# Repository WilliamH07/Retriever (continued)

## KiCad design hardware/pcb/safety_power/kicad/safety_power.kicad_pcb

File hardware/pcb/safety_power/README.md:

# safety_power

> ⚠️ **v2.0-draft — do not manufacture before M1, M2, M10, M12, PACK_ID, P1–P3 and a
> review by an electronics engineer.** Schematic and layout are generated and checked
> (ERC/DRC below); nothing has been built, measured or reviewed. This board switches
> 42 V / 30 A on a 474 Wh lithium pack. Every choice, every computed value, what is not
> verified and what an expert must look at: [`decisions.md`](decisions.md) (French).
> Brief: [`cahier-des-charges.md`](cahier-des-charges.md).

| | |
|---|---|
| Status | **v2.0-draft** — ERC 0 · DRC 0 (`--schematic-parity --severity-all`) · 0 unconnected · parity 0. Not fabricated, not reviewed |
| Size | 210 × 160 mm, 4 layers, 2 oz outer copper, 6 × M3 (unplated, no chassis bond) |
| Parts | 344 symbols, 350 footprints; JLCPCB BOM 111 lines / 298 placements (THT connectors and modules included); hand-fitted: 4 fuse holders, ESP32 sockets, ring lugs |
| Contactor | `TPS48100QDGXRQ1` (in stock at JLCPCB, C43131316) + 2 × `IPB017N10N5LF` back-to-back, 1 mΩ 4-wire shunt, SCP ≈ 99 A / 100 µs latched |
| Rails (upstream of the contactor) | 5 V 3.5 A and 12 V AUX 2 A on `TPS54360B`; 12 V 30 W isolated `URB4812YMD-30WR3`; 3.3 V `AP2112K` |
| Sources | [`kicad/`](kicad/) — KiCad 10 project, **generated** by [`scripts/build.py`](scripts/build.py) (+ [`scripts/splib.py`](scripts/splib.py) for the symbols and footprints KiCad lacks) |
| Fabrication | [`fab/`](fab/) — Gerber zip, JLCPCB BOM and placement, schematic PDF, assembly drawing, renders |

Rebuild everything: `./build.sh` (placement, power copper, Freerouting, then a
clean-up pass by [`scripts/patchroute.py`](scripts/patchroute.py); 30–60 minutes) then
`./fab.sh`. Freerouting is not deterministic: a rebuild gives an equivalent board, not an
identical one, and may leave a connection for the clean-up pass or for hand routing. The
committed board took one hand-placed via (net `EFUSE_FLT_N`, near U14) after that pass. Toolchain: [`../outils.md`](../outils.md). Do not edit the
KiCad files by hand: change `scripts/build.py` and rebuild.

## What it does

The board that decides whether the robot may move.

- **Battery in** on two M5 ring-lug studs (`J1`), after the manual battery switch and the
  MRBF fuse.
- **Static contactor**: `TPS48100-Q1` driving two `IPB017N10N5LF` back to back, common
  source, so the switch blocks both discharge and regeneration. Two independent gate
  drives on `INP1`/`INP2` make a per-transistor stuck-switch test possible (`MID` node
  read by an ADS1115). Bidirectional `SMCJ48CA` across the switch, Schottky freewheel on
  the bus, 150 Ω turn-off gate resistors.
- **Precharge** through an off-board 10 Ω / 25 W resistor (`J13`), P-FET driven by the
  ESP32, not by the controller.
- **Brake chopper**: analogue comparator powered **by the bus itself** through a 100 V LDO,
  42.5 V on / 41.8 V off, 22 Ω / 100 W off-board (`J12`). It also serves as the active bus
  discharge when the ESP32 asks for it with the contactor open.
- **Four motor branches**, each with a MINI 58 V 25 A blade fuse in a PCB holder, a 2 mΩ
  4-wire shunt and an `INA228` whose bus input sits after the fuse (blown-fuse detection).
- **Hotel rails taken upstream of the contactor** (decision D2), so the SAFETY ESP32, the
  `/SAFE` pull-up and `5V_BRAKE` survive an open contactor.
- **SAFETY ESP32** (DevKitC V4 on sockets), CAN (`TCAN1042HV`), the **single** `/SAFE`
  pull-up through the mushroom's NC contact and the single pull-down, a `TPL5010`
  watchdog **latched** by a D flip-flop together with an ACS758 window comparator
  (± 35 A), an isolated BMS UART, the remote BNO085, two fans, two WS2812B strips and a
  temperature input.
- **One ground bond**, `★ GND STAR`, between `GND_LOGIC` and `BUS_N`, silkscreened.

## Layout

Strict zoning: the 42 V power zone across the top 64 mm, the signal zone below, split
along a line where the inner and bottom ground planes change from `BUS_N` to `GND_LOGIC`.
The high-current copper (battery, drain planes, bus bar, branches, chopper) is drawn by
the script as polygons on F.Cu with stitched B.Cu/In1 return planes, and is handed to the
autorouter as planes: Freerouting only routes signals. Clearance on 42 V power copper is
0.5 mm.

**Routing quality is draft quality.** The autorouter used the inner ground layer (In1) for
about 450 short signal segments, which cuts the `GND_LOGIC`/`BUS_N` planes into a lace,
and it routed both switching regulators. Both must be redone by hand before anyone orders
this board (see *Relecture experte* in `decisions.md`).

## Blocking measurements

M1 (BMS cut-off), M2 (pack resistance), M10 (bus capacitance), M12 (driver input
capacitor rating), PACK_ID (pack and BMS labels), P1–P3 (ESP32 module footprint, pin
order, PSRAM variant). See [`docs/measurements/`](../../../docs/measurements/).

Pinout: `boards.safety_power` in [`hardware/icd.yaml`](../../icd.yaml). The board departs
from ICD v1.2 in a few places (ring-lug studs, MINI 58 V fuses, new `5V_BRAKE`
connectors J22/J23, BMS on JST GH): the proposed v1.3 changes are listed at the end of
[`decisions.md`](decisions.md).

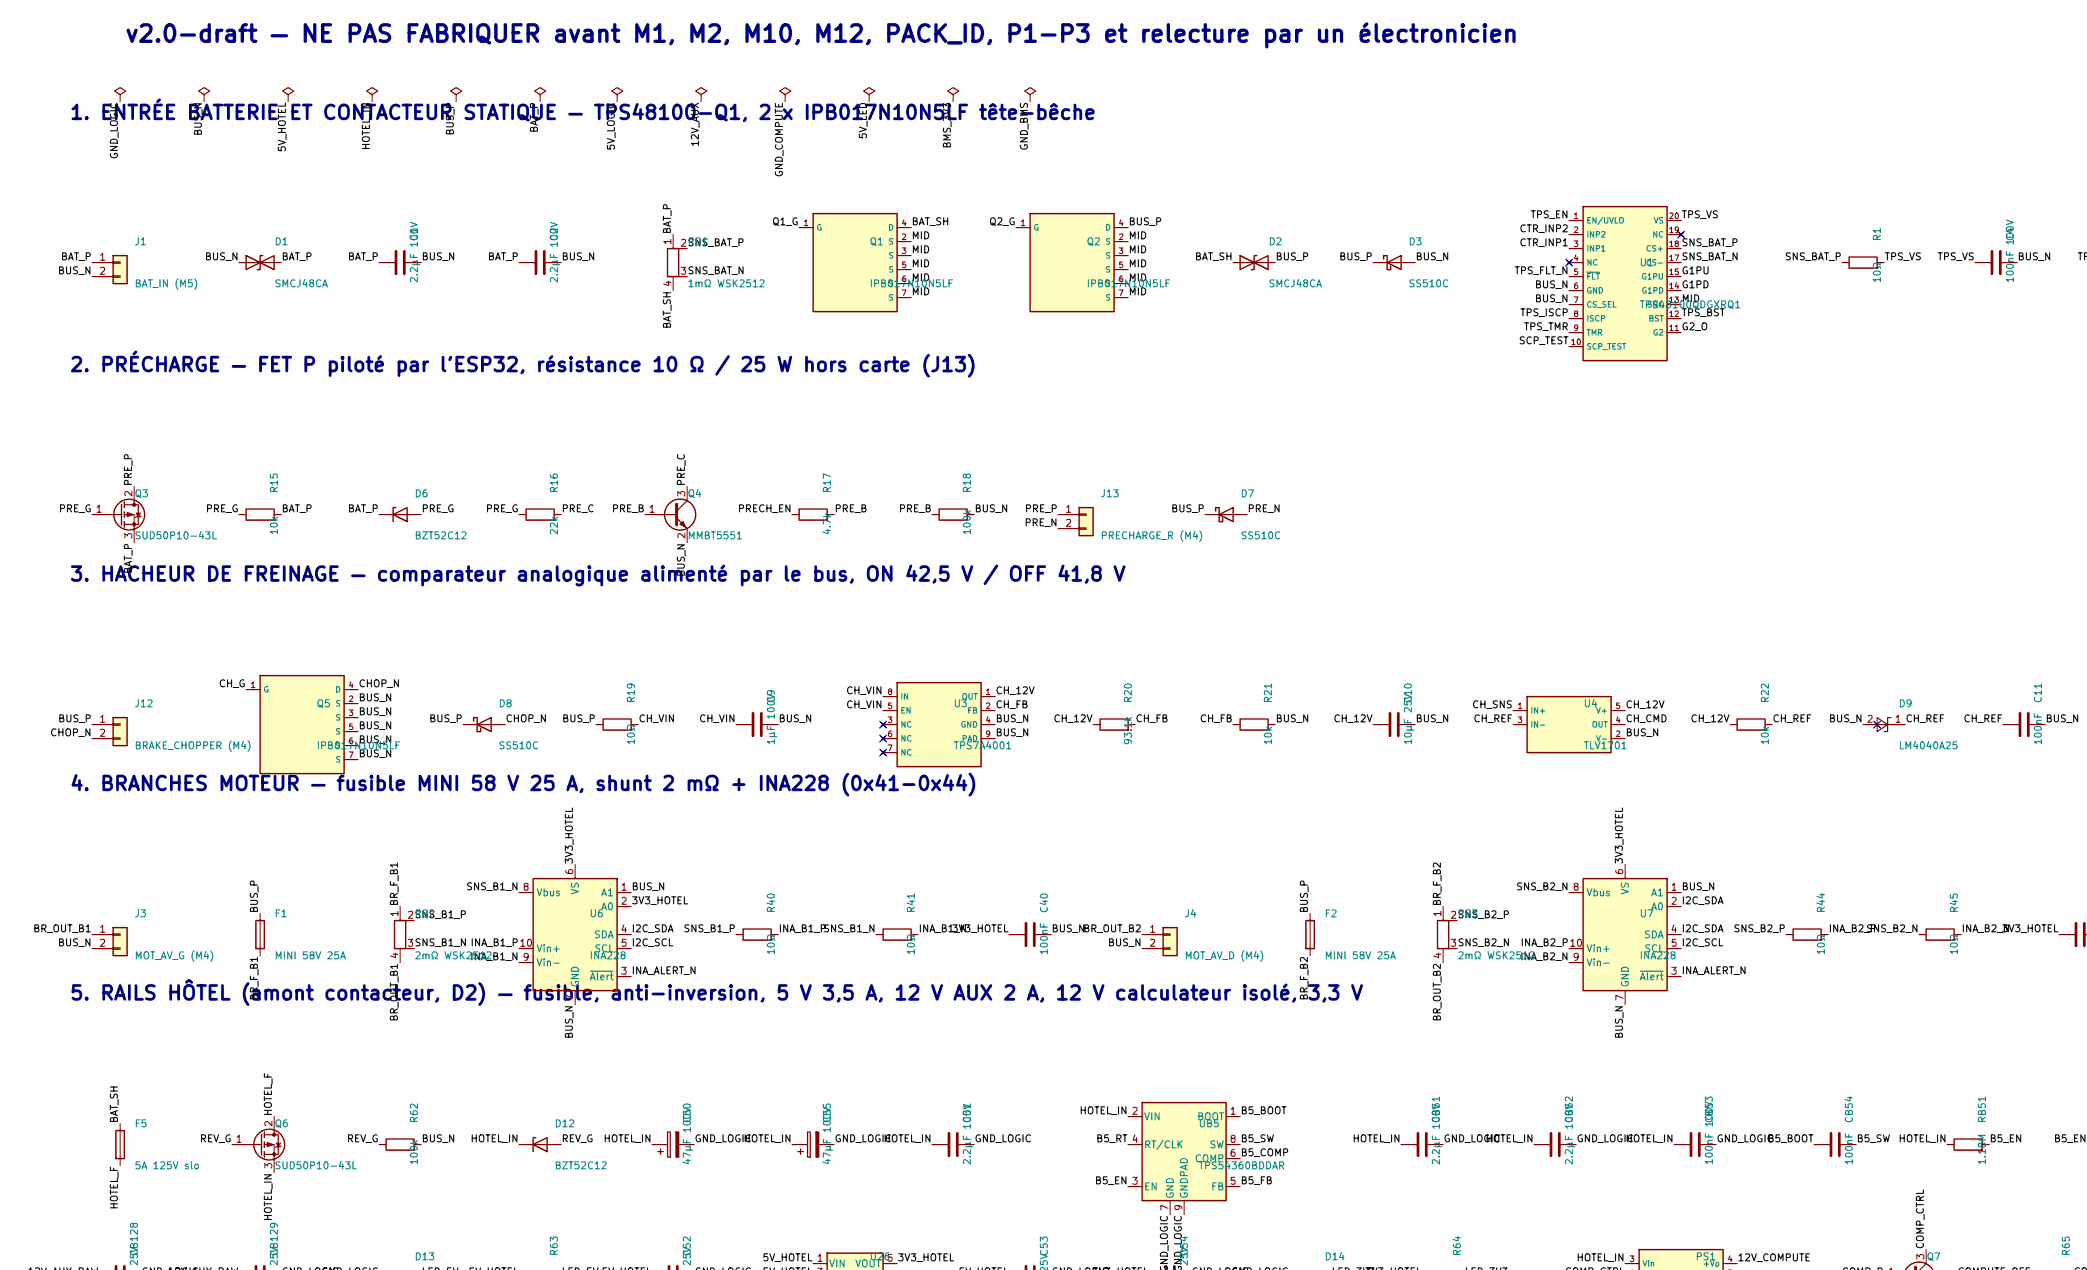
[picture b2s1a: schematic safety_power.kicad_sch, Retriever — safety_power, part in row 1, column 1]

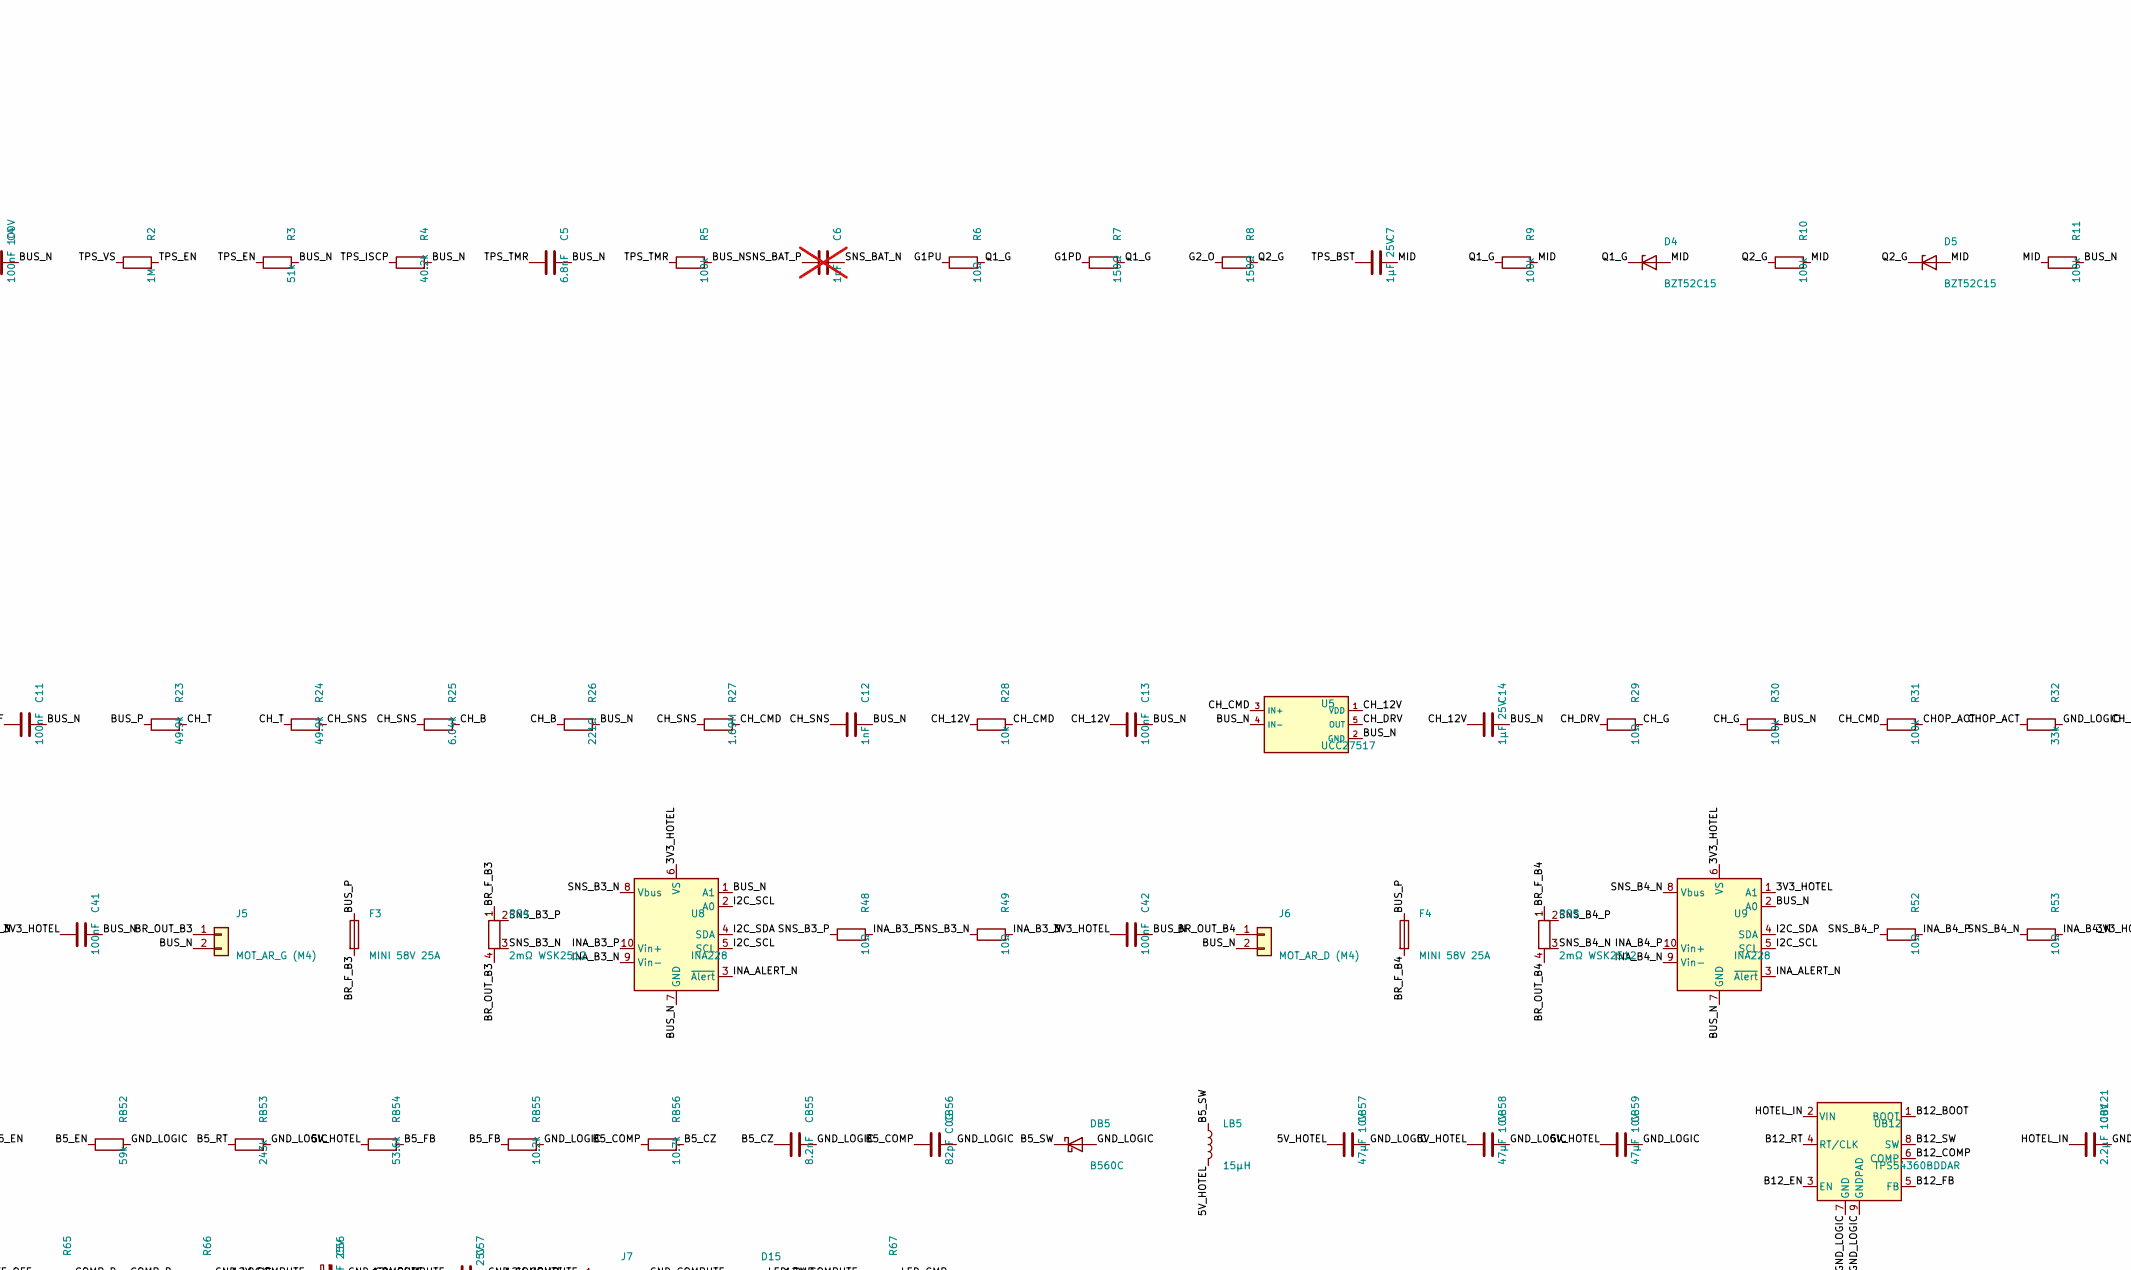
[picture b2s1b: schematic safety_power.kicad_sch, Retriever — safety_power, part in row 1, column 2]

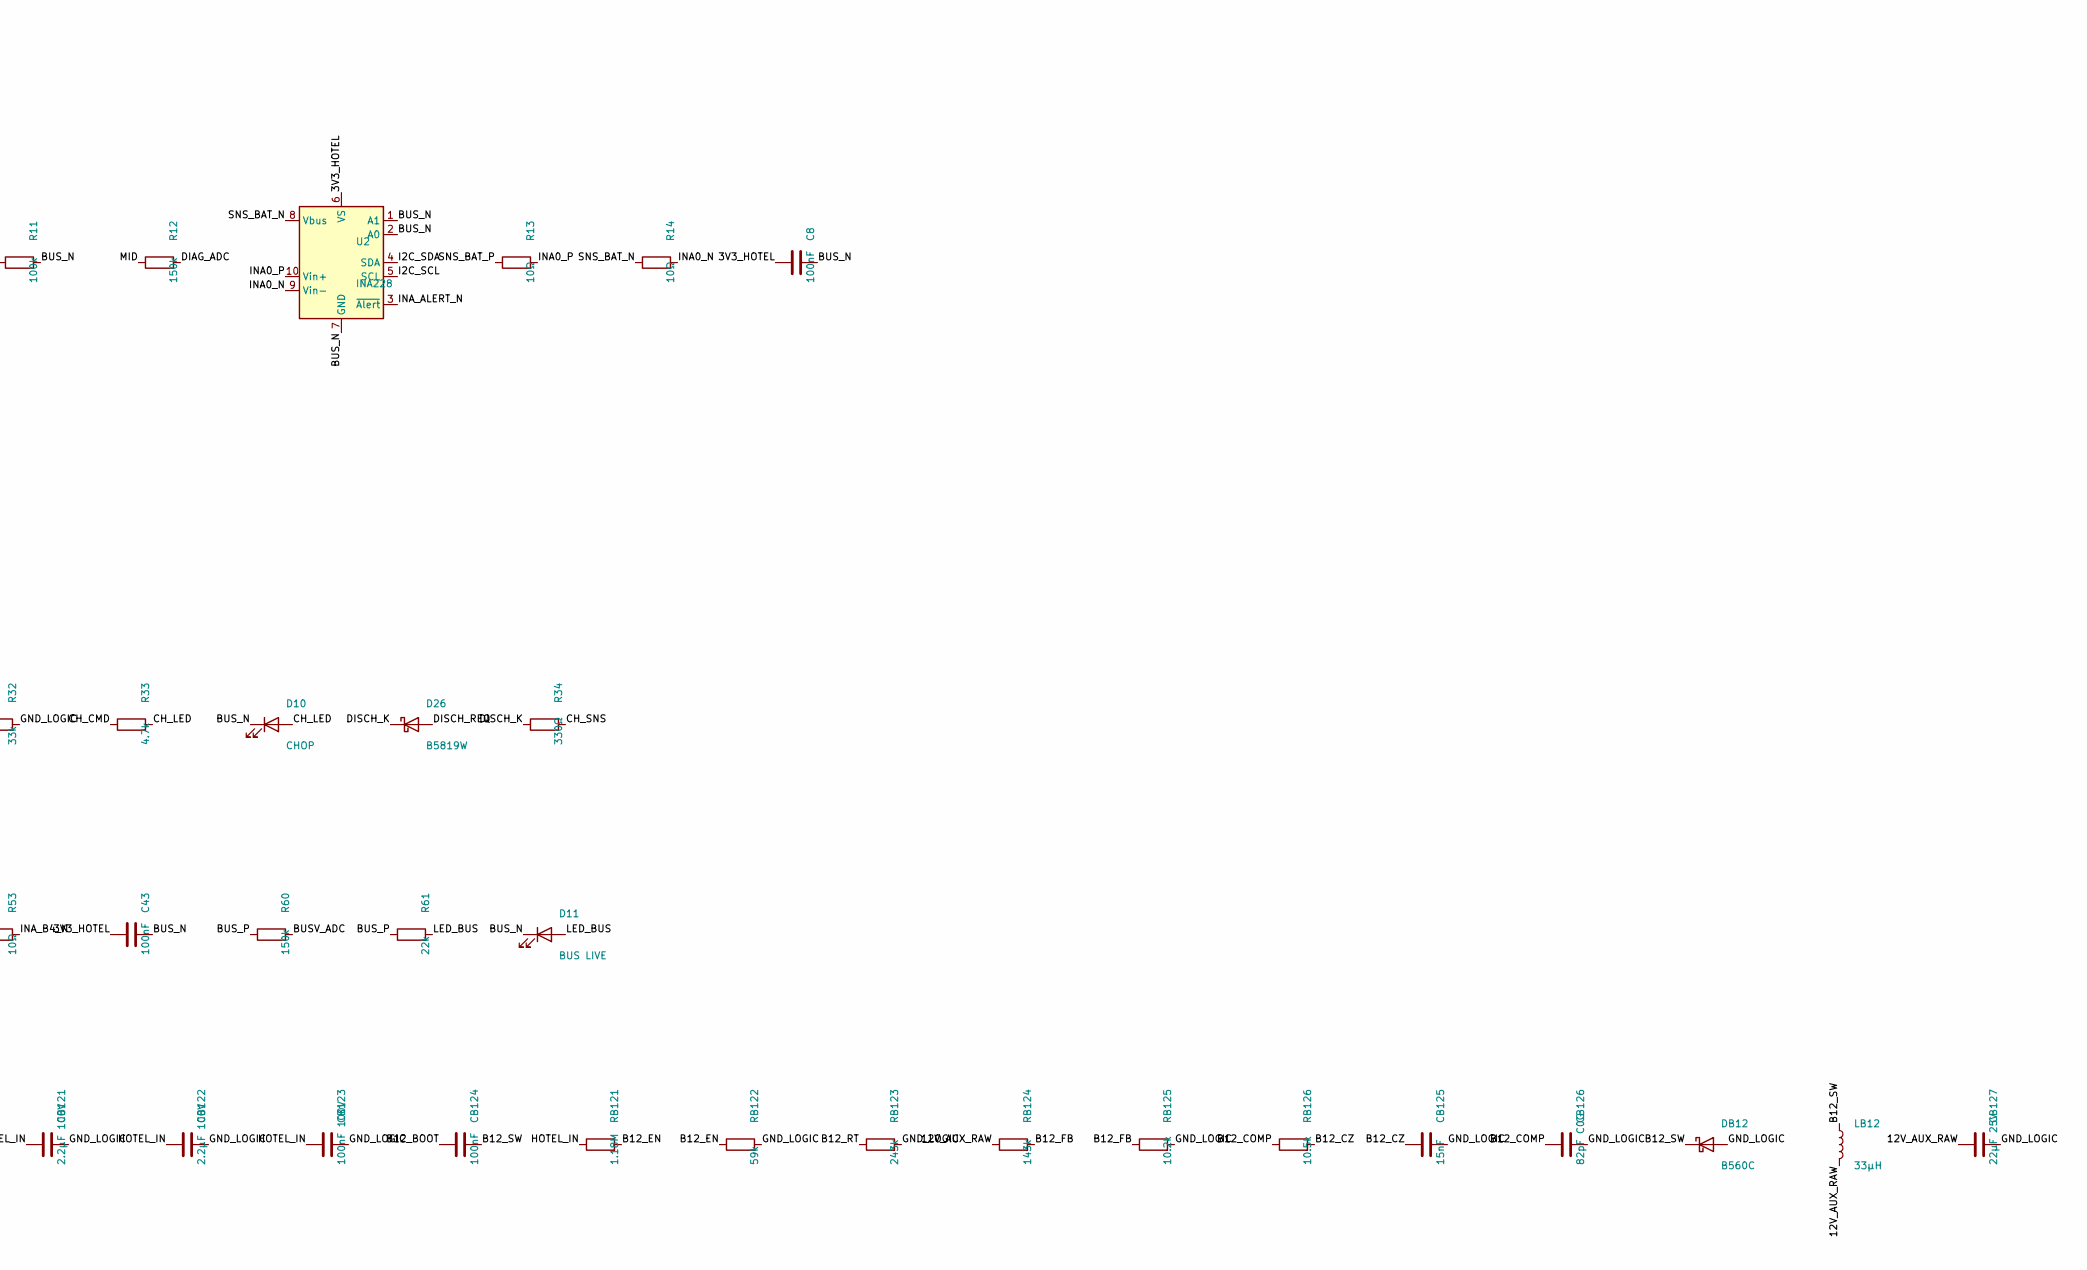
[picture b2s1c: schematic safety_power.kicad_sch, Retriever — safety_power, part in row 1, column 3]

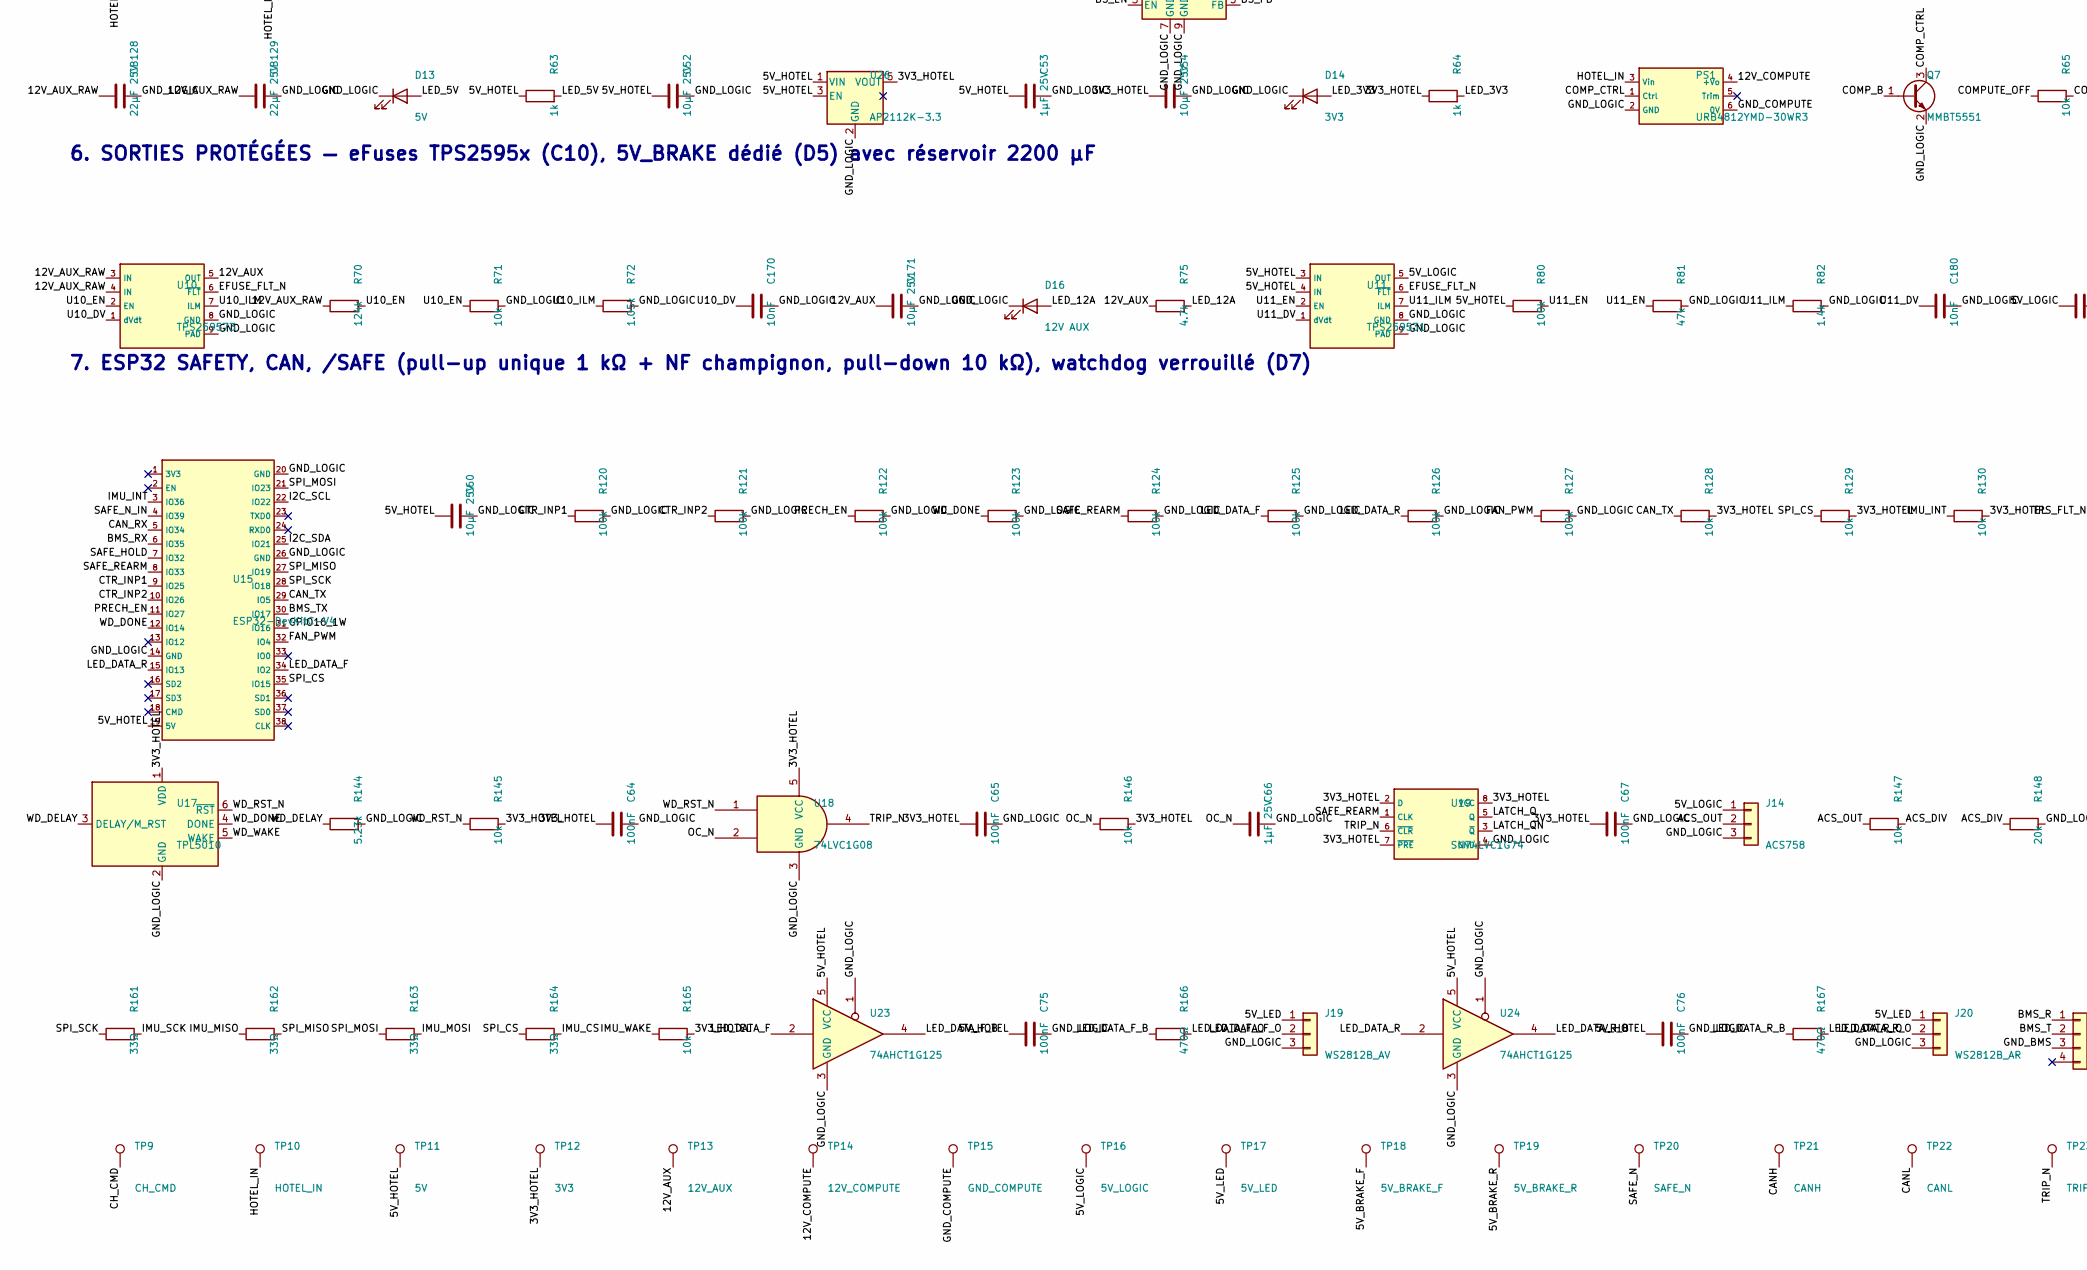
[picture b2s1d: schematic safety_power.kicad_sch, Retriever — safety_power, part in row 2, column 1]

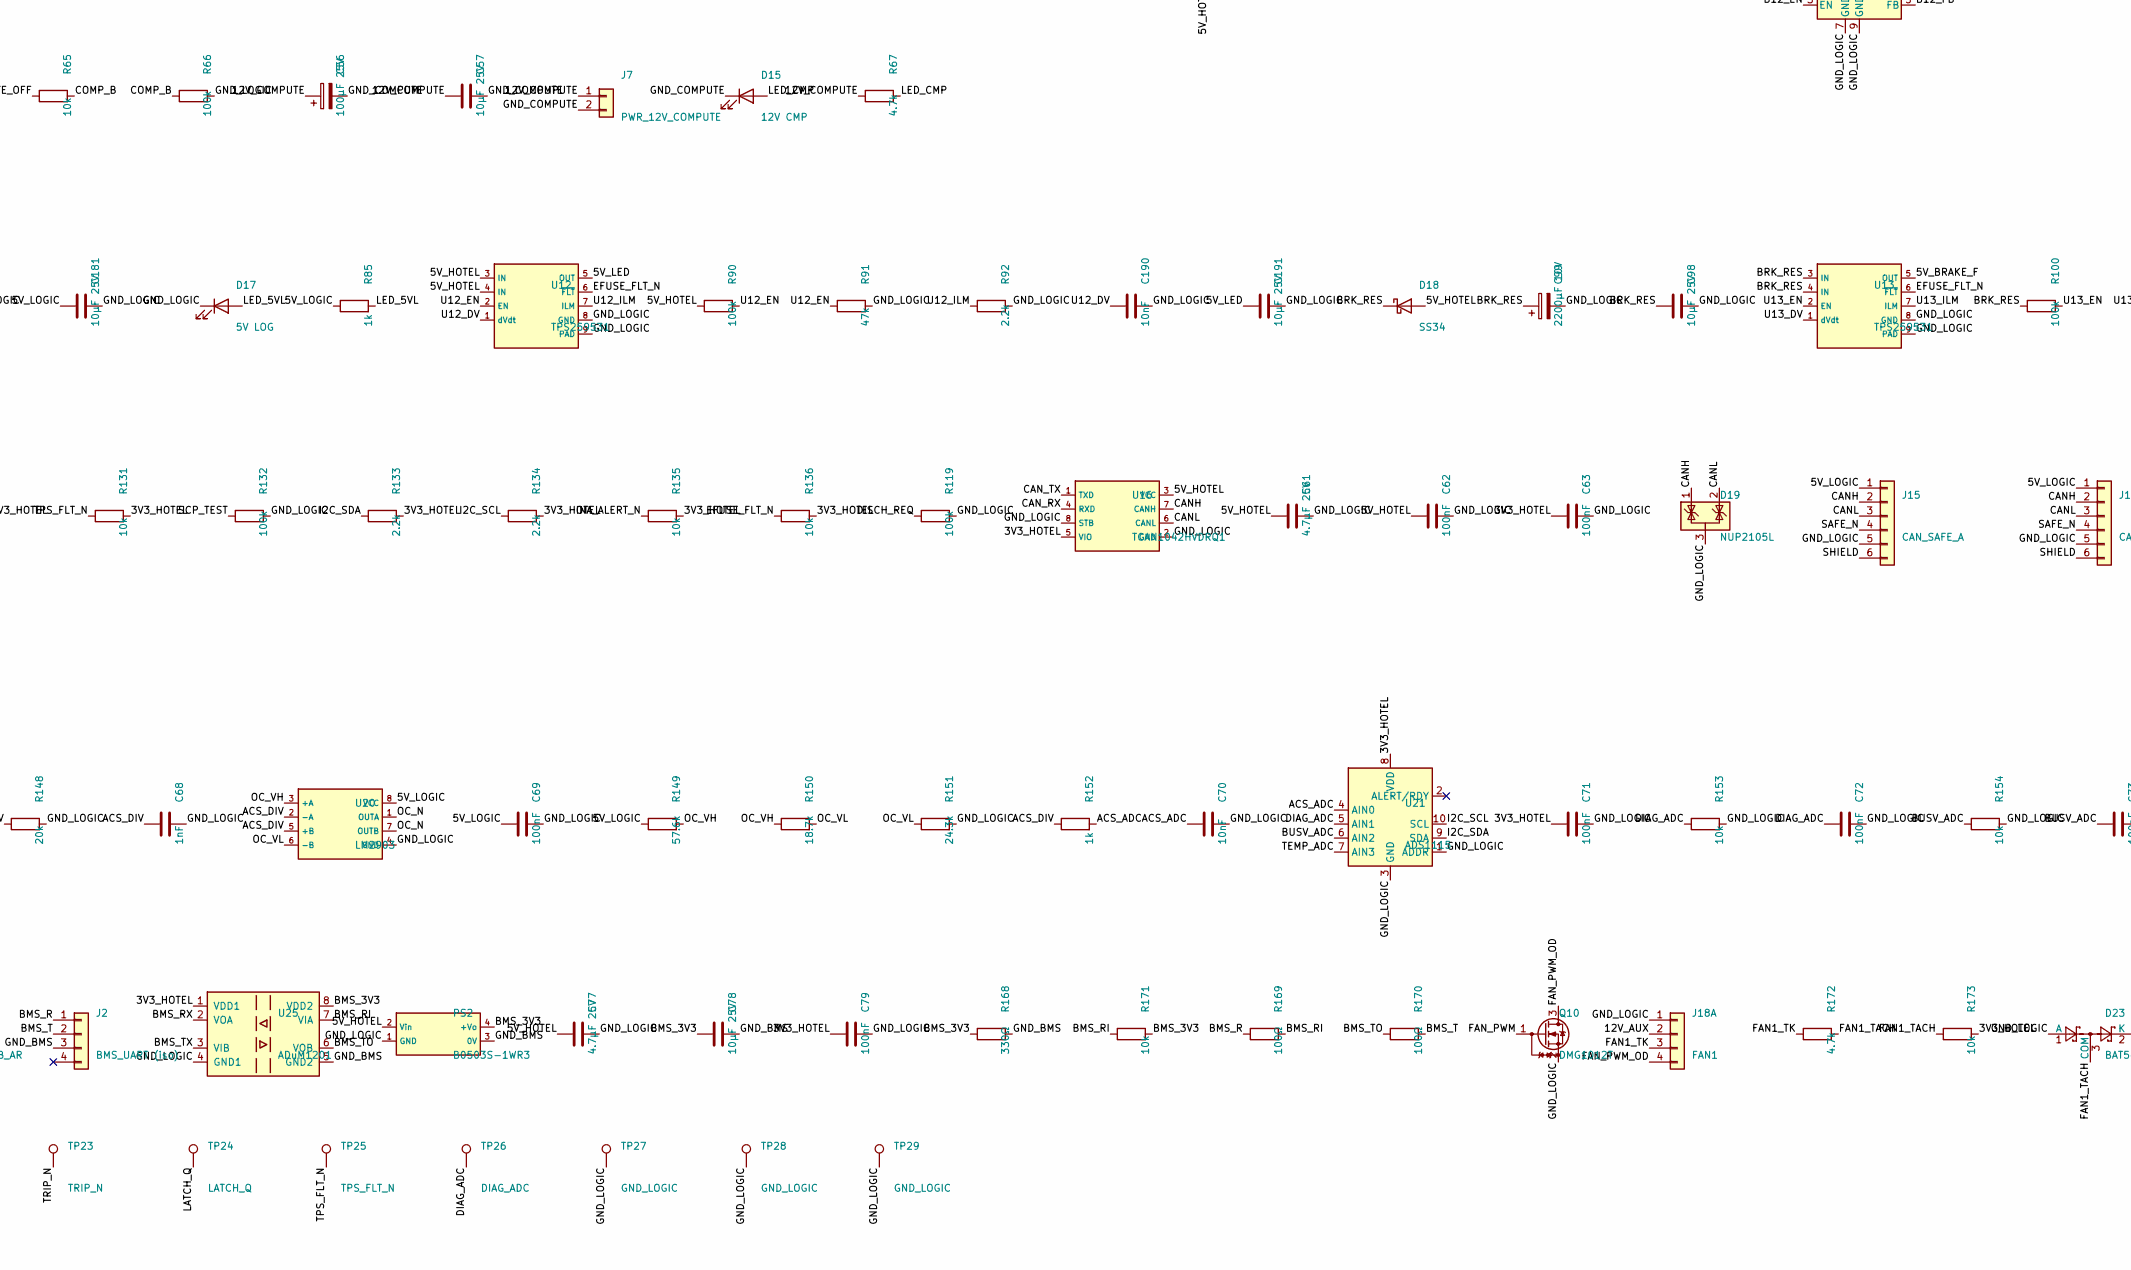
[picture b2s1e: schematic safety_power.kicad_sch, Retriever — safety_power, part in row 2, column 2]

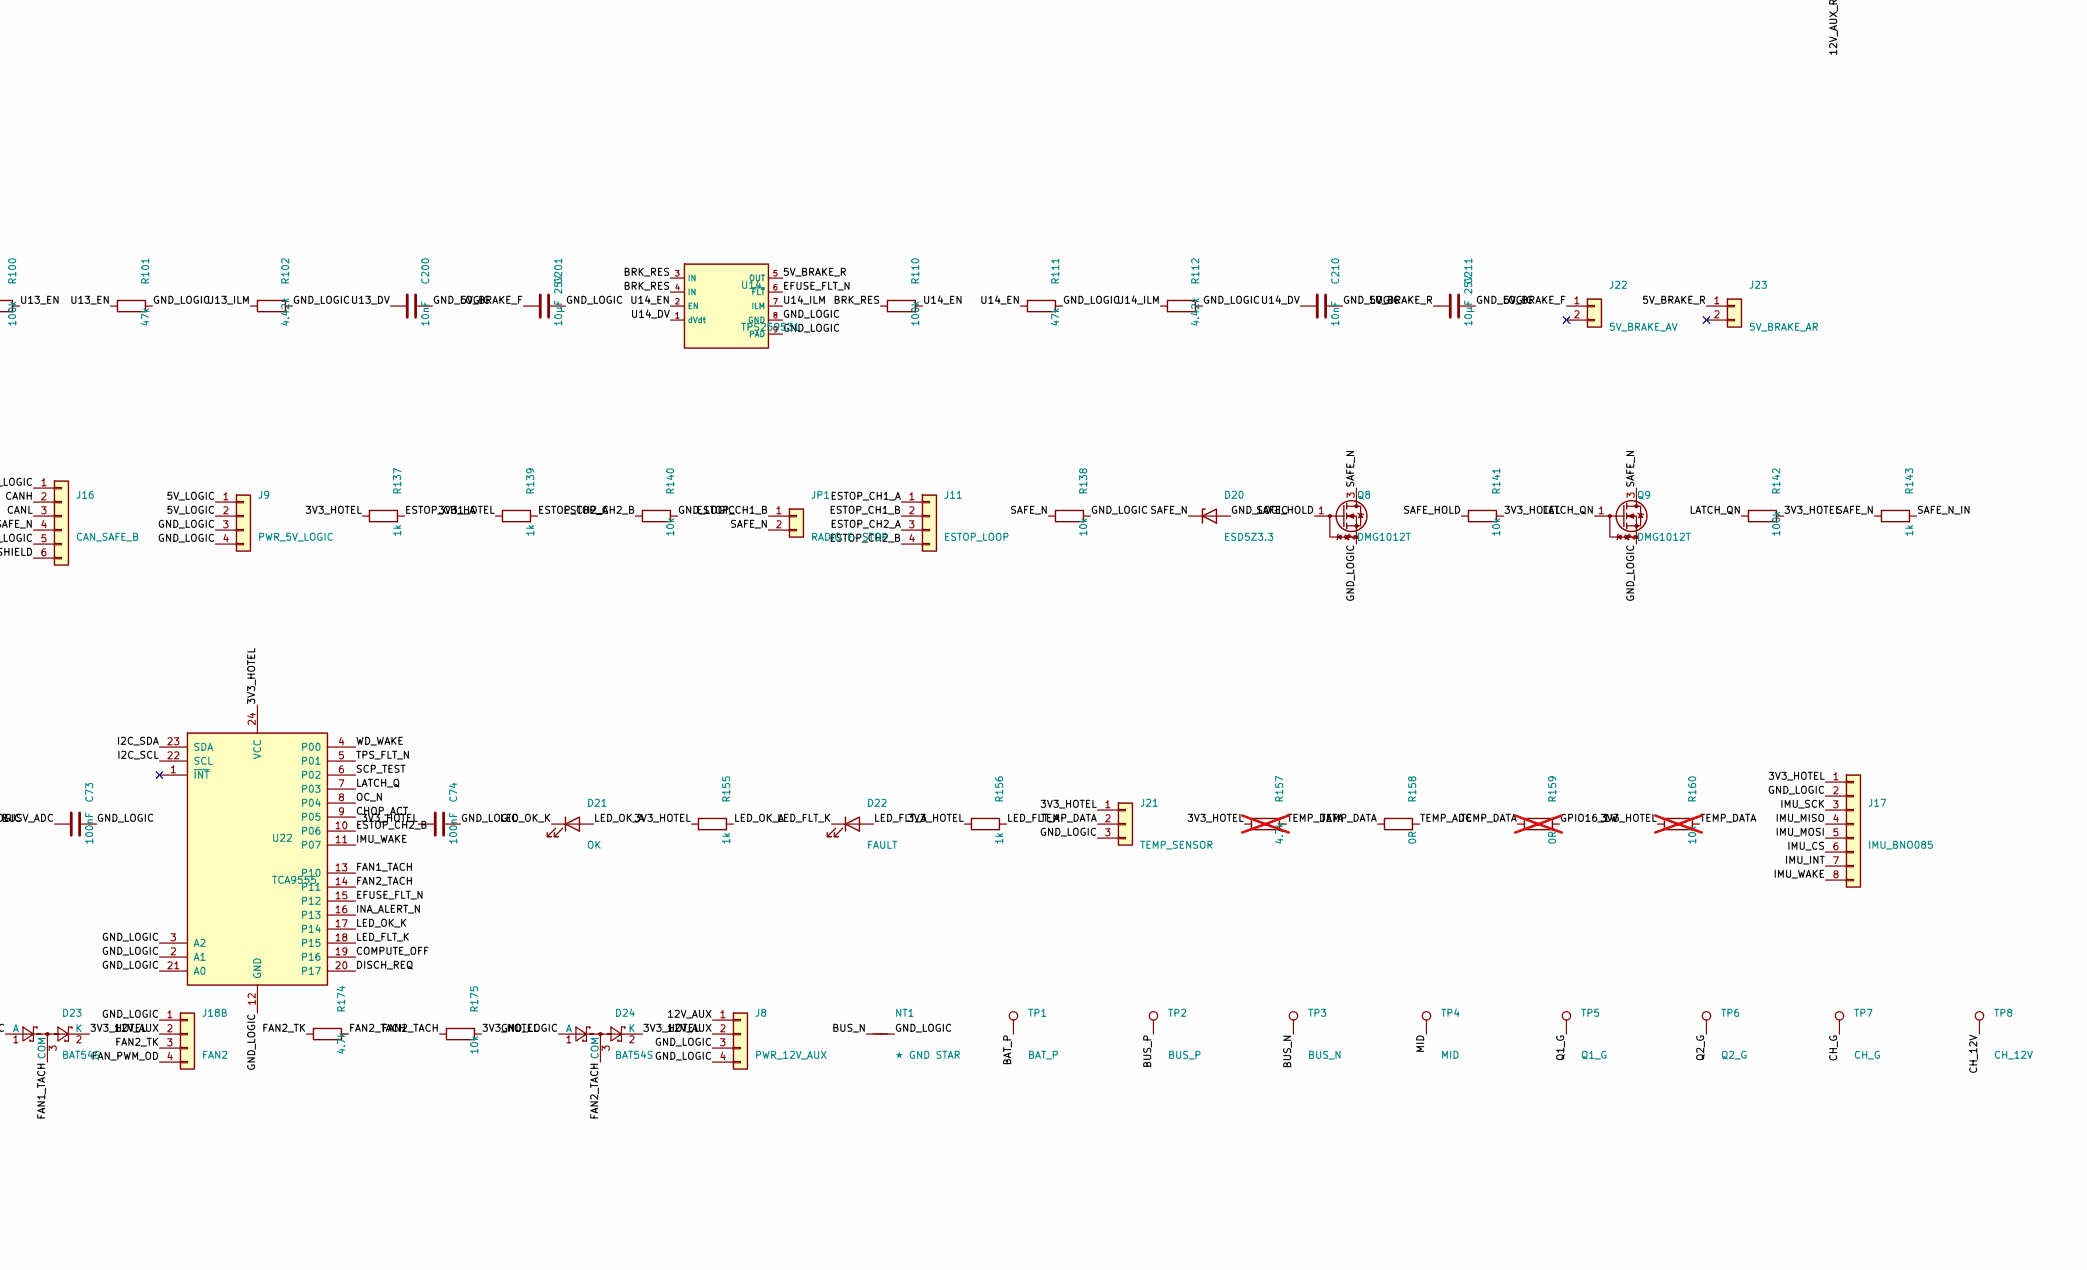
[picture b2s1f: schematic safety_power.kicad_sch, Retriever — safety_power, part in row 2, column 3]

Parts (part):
C1, C2, C51: 2.2µF 100V; C_1210_3225Metric; MPN FS32X225K101EGG; LCSC C153036
C4: 100nF 100V; C_0603_1608Metric; MPN 0603B104K101NT; LCSC C88219
C5: 6.8nF; C_0603_1608Metric; MPN 0603B682K500NT; LCSC C1631
C6: 1nF; C_0603_1608Metric; MPN CL10B102KB8NNNC; LCSC C1588; not fitted
C7, C14, C53, C66: 1µF 25V; C_0603_1608Metric; MPN CL10A105KA8NNNC; LCSC C5673
C8, C11, C13, C40, C41, C42, C43, C62, C63, C64, C65, C67, C69, C71, C72, C73, C74, C75, C76, C79: 100nF; C_0603_1608Metric; MPN CC0603KRX7R9BB104; LCSC C14663
C9: 1µF 100V; C_0805_2012Metric; MPN HMK212BC7105KGHTE; LCSC C385977
C10, C52, C54, C57, C60, C78, C98, C171, C181, C191, C201, C211: 10µF 25V; C_0805_2012Metric; MPN CL21A106KAYNNNE; LCSC C15850
C12, C68: 1nF; C_0603_1608Metric; MPN CL10B102KB8NNNC; LCSC C1588
C50, C55: 47µF 100V; CP_Elec_8x10; MPN RV100V47M8X10; LCSC C48935391
C56: 100µF 25V; CP_Elec_6.3x7.7; MPN RVT100UF25V67RV0011; LCSC C2836443
C61, C77: 4.7µF 25V; C_0805_2012Metric; MPN CL21A475KAQNNNE; LCSC C1779
C70, C170, C180, C190, C200, C210: 10nF; C_0603_1608Metric; MPN 0603B103K500NT; LCSC C57112
C99: 2200µF 10V; CP_Radial_D10.0mm_P5.00mm; MPN ERA10V2200M10X16; LCSC C49256788
CB51, CB52, CB121, CB122: 2.2µF 100V; C_1210_3225Metric; MPN FS32X225K101EGG; LCSC C153036
CB53, CB123: 100nF 100V; C_0603_1608Metric; MPN 0603B104K101NT; LCSC C88219
CB54, CB124: 100nF; C_0603_1608Metric; MPN CC0603KRX7R9BB104; LCSC C14663
CB55: 8.2nF; C_0603_1608Metric; MPN 0603B822K500NT; LCSC C1322360
CB56, CB126: 82pF C0G; C_0603_1608Metric; MPN CC0603JRNPO9BN820; LCSC C107056
CB57, CB58, CB59: 47µF 10V; C_1210_3225Metric; MPN GRM32ER71A476KE15L; LCSC C84494
CB125: 15nF; C_0603_1608Metric; MPN CC0603KRX7R9BB153; LCSC C107076
CB127, CB128, CB129: 22µF 25V; C_1210_3225Metric; MPN CL32A226KAJNNNE; LCSC C52306
D1, D2: SMCJ48CA; D_SMC; MPN SMCJ48CA bidirectional; LCSC C151287
D3, D7, D8: SS510C; D_SMC; MPN SS510C 100 V 5 A; LCSC C19229
D4, D5: BZT52C15; D_SOD-123; MPN BZT52C15; LCSC C173427
D6, D12: BZT52C12; D_SOD-123; MPN BZT52C12; LCSC C43491
D9: LM4040A25; SOT-23; MPN TI LM4040A25IDBZR; LCSC C9421
D10: CHOP; LED_0603_1608Metric; MPN KT-0603R; LCSC C2286
D11: BUS LIVE; LED_0603_1608Metric; MPN KT-0603R; LCSC C2286
D13: 5V; LED_0603_1608Metric; MPN Everlight 19-217/GHC; LCSC C72043
D14: 3V3; LED_0603_1608Metric; MPN Everlight 19-217/GHC; LCSC C72043
D15: 12V CMP; LED_0603_1608Metric; MPN Everlight 19-217/GHC; LCSC C72043
D16: 12V AUX; LED_0603_1608Metric; MPN Everlight 19-217/GHC; LCSC C72043
D17: 5V LOG; LED_0603_1608Metric; MPN Everlight 19-217/GHC; LCSC C72043
D18: SS34; D_SMA; MPN SS34; LCSC C8678
D19: NUP2105L; SOT-23; MPN onsemi NUP2105LT1G; LCSC C14486
D20: ESD5Z3.3; D_SOD-523; MPN ESD5Z3.3; LCSC C397781
D21: OK; LED_0603_1608Metric; MPN Everlight 19-217/GHC; LCSC C72043
D22: FAULT; LED_0603_1608Metric; MPN KT-0603R; LCSC C2286
D23, D24: BAT54S; SOT-23; MPN onsemi BAT54SLT1G; LCSC C19726
D26: B5819W; D_SOD-123; MPN B5819W; LCSC C8598
DB5, DB12: B560C; D_SMC; MPN Diodes B560C-13-F; LCSC C85100
F1, F2, F3, F4: MINI 58V 25A; Fuseholder_Blade_Mini_Keystone_3568; MPN Keystone 3568-20 holder + Littelfuse 09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
F5: 5A 125V slo; Fuse_Littelfuse-NANO2-451_453; MPN Littelfuse 0452005.MRL; LCSC C66503
J1: BAT_IN (M5); RingLug_M5_2P_P26; MPN plated holes, ring lugs M5
J2: BMS_UART (iso); JST_GH_SM04B-GHS-TB_1x04-1MP_P1.25mm_Horizontal; MPN JST SM04B-GHS-TB; LCSC C189895
J3: MOT_AV_G (M4); RingLug_M4_2P_P13; MPN plated holes, ring lugs M4
J4: MOT_AV_D (M4); RingLug_M4_2P_P13; MPN plated holes, ring lugs M4
J5: MOT_AR_G (M4); RingLug_M4_2P_P13; MPN plated holes, ring lugs M4
J6: MOT_AR_D (M4); RingLug_M4_2P_P13; MPN plated holes, ring lugs M4
J7: PWR_12V_COMPUTE; JST_XH_B2B-XH-A_1x02_P2.50mm_Vertical; MPN JST B2B-XH-A; LCSC C265283
J8: PWR_12V_AUX; Molex_Micro-Fit_3.0_43650-0415_1x04_P3.00mm_Vertical; MPN Molex 43650-0415; LCSC C293547
J9: PWR_5V_LOGIC; Molex_Micro-Fit_3.0_43650-0415_1x04_P3.00mm_Vertical; MPN Molex 43650-0415; LCSC C293547
J11: ESTOP_LOOP; Molex_Micro-Fit_3.0_43650-0415_1x04_P3.00mm_Vertical; MPN Molex 43650-0415; LCSC C293547
J12: BRAKE_CHOPPER (M4); RingLug_M4_2P_P13; MPN plated holes, ring lugs M4
J13: PRECHARGE_R (M4); RingLug_M4_2P_P13; MPN plated holes, ring lugs M4
J14: ACS758; Molex_Micro-Fit_3.0_43650-0315_1x03_P3.00mm_Vertical; MPN Molex 43650-0315; LCSC C293546
J15: CAN_SAFE_A; Molex_Micro-Fit_3.0_43650-0615_1x06_P3.00mm_Vertical; MPN Molex 43650-0615; LCSC C505231
J16: CAN_SAFE_B; Molex_Micro-Fit_3.0_43650-0615_1x06_P3.00mm_Vertical; MPN Molex 43650-0615; LCSC C505231
J17: IMU_BNO085; JST_GH_SM08B-GHS-TB_1x08-1MP_P1.25mm_Horizontal; MPN JST SM08B-GHS-TB; LCSC C265111
J18A: FAN1; FanPinHeader_1x04_P2.54mm_Vertical; MPN Molex 47053-1000; LCSC C240840
J18B: FAN2; FanPinHeader_1x04_P2.54mm_Vertical; MPN Molex 47053-1000; LCSC C240840
J19: WS2812B_AV; Molex_Micro-Fit_3.0_43650-0315_1x03_P3.00mm_Vertical; MPN Molex 43650-0315; LCSC C293546
J20: WS2812B_AR; Molex_Micro-Fit_3.0_43650-0315_1x03_P3.00mm_Vertical; MPN Molex 43650-0315; LCSC C293546
J21: TEMP_SENSOR; Molex_Micro-Fit_3.0_43650-0315_1x03_P3.00mm_Vertical; MPN Molex 43650-0315; LCSC C293546
J22: 5V_BRAKE_AV; Molex_Micro-Fit_3.0_43650-0215_1x02_P3.00mm_Vertical; MPN Molex 43650-0215; LCSC C293740
J23: 5V_BRAKE_AR; Molex_Micro-Fit_3.0_43650-0215_1x02_P3.00mm_Vertical; MPN Molex 43650-0215; LCSC C293740
JP1: RADIO E-STOP; PinHeader_1x02_P2.54mm_Vertical; MPN 2.54 mm 1x2 header + jumper; LCSC C492401
LB5: 15µH; L_TaiTech_TMPC1265_13.5x12.5mm; MPN Bourns SRP1265A-150M; LCSC C189912
LB12: 33µH; L_TaiTech_TMPC1265_13.5x12.5mm; MPN MDA1365-330M; LCSC C2847586
NT1: ★ GND STAR; NetTie_GND_STAR_4mm
PS1: URB4812YMD-30WR3; Mornsun_URB_YMD-30WR3_1x1in; MPN Mornsun URB4812YMD-30WR3; LCSC C22458769
PS2: B0503S-1WR3; PinHeader_1x04_P2.54mm_Vertical; MPN Mornsun B0503S-1WR3; LCSC C5369462
Q1, Q2, Q5: IPB017N10N5LF; TO-263-7_TabPin4_NoPin4; MPN Infineon IPB017N10N5LFATMA1; LCSC C3289286
Q3, Q6: SUD50P10-43L; TO-252-2; MPN SUD50P10-43L-TP; LCSC C41408040
Q4, Q7: MMBT5551; SOT-23; MPN MMBT5551; LCSC C2145
Q8, Q9, Q10: DMG1012T; SOT-523; MPN Diodes DMG1012T-7; LCSC C20512
R1, R6, R13, R14, R19, R29, R40, R41, R44, R45, R48, R49, R52, R53: 10Ω; R_0603_1608Metric; MPN 0603WAF100JT5E; LCSC C22859
R2: 1M; R_0603_1608Metric; MPN 0603WAF1004T5E; LCSC C22935
R3: 51k; R_0603_1608Metric; MPN 0603WAF5102T5E; LCSC C23196
R4: 40.2k; R_0603_1608Metric; MPN 0603WAF4022T5E; LCSC C12447
R5, R9, R10, R11, R18, R30, R31, R62, R66, R80, R90, R100, R110, R119, R120, R121, R122, R123, R124, R125, R126, R127, R132, R142: 100k; R_0603_1608Metric; MPN 0603WAF1003T5E; LCSC C25803
R7, R8: 150Ω; R_0603_1608Metric; MPN 0603WAF1500T5E; LCSC C22808
R12, R60: 150k; R_0603_1608Metric; MPN 0603WAF1503T5E; LCSC C22807
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
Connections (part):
/3V3_HOTEL: C8.1, C40.1, C41.1, C42.1, C43.1, C54.1, C63.1, C64.1, C65.1, C67.1, C71.1, C74.1, C79.1, D23.2 (K), D24.2 (K), J17.1, J21.1, R64.1, R128.2, R129.2, R130.2, R131.2, R133.2, R134.2, R135.2, R136.2, R137.1, R139.1, R141.2, R142.2, R145.2, R146.2, R155.1, R156.1, R157.1, R160.1, R165.2, R173.2, R175.2, TP12.1, U2.6 (VS), U6.2 (A0), U6.6 (VS), U7.6 (VS), U8.6 (VS), U9.1 (A1), U9.6 (VS), U16.5 (VIO), U17.1 (VDD), U18.5 (VCC), U19.2 (D), U19.7 (~PRE), U19.8 (VCC), U21.8 (VDD), U22.24 (VCC), U25.1 (VDD1), U26.5 (VOUT)
/5V_BRAKE_F: C201.1, J22.1, TP18.1, U13.5 (OUT)
/5V_BRAKE_R: C211.1, J23.1, TP19.1, U14.5 (OUT)
/5V_HOTEL: C52.1, C53.1, C60.1, C61.1, C62.1, C75.1, C76.1, C77.1, CB57.1, CB58.1, CB59.1, D18.2 (A), LB5.2, PS2.2 (Vin), R63.1, R80.1, R90.1, RB54.1, TP11.1, U11.3 (IN), U11.4 (IN), U12.3 (IN), U12.4 (IN), U15.19 (5V), U16.3 (VCC), U23.5 (VCC), U24.5 (VCC), U26.1 (VIN), U26.3 (EN)
/5V_LED: C191.1, J19.1, J20.1, TP17.1, U12.5 (OUT)
/5V_LOGIC: C69.1, C181.1, J9.1, J9.2, J14.1, J15.1, J16.1, R85.1, R149.1, TP16.1, U11.5 (OUT), U20.8 (VCC)
/12V_AUX: C171.1, J8.1, J8.2, J18A.2, J18B.2, R75.1, TP13.1, U10.5 (OUT)
/12V_AUX_RAW: CB127.1, CB128.1, CB129.1, LB12.2, R70.1, RB124.1, U10.3 (IN), U10.4 (IN)
/12V_COMPUTE: C56.1, C57.1, J7.1, PS1.4 (+Vo), R67.1, TP14.1
/ACS_ADC: C70.1, R152.2, U21.4 (AIN0)
/ACS_DIV: C68.1, R147.2, R148.1, R152.1, U20.2 (-A), U20.5 (+B)
/ACS_OUT: J14.2, R147.1
/B5_BOOT: CB54.1, UB5.1 (BOOT)
/B5_COMP: CB56.1, RB56.1, UB5.6 (COMP)
/B5_CZ: CB55.1, RB56.2
/B5_EN: RB51.2, RB52.1, UB5.3 (EN)
/B5_FB: RB54.2, RB55.1, UB5.5 (FB)
/B5_RT: RB53.1, UB5.4 (RT/CLK)
/B5_SW: CB54.2, DB5.1 (K), LB5.1, UB5.8 (SW)
/B12_BOOT: CB124.1, UB12.1 (BOOT)
/B12_COMP: CB126.1, RB126.1, UB12.6 (COMP)
/B12_CZ: CB125.1, RB126.2
/B12_EN: RB121.2, RB122.1, UB12.3 (EN)
/B12_FB: RB124.2, RB125.1, UB12.5 (FB)
/B12_RT: RB123.1, UB12.4 (RT/CLK)
/B12_SW: CB124.2, DB12.1 (K), LB12.1, UB12.8 (SW)
/BAT_P: C1.1, C2.1, D1.2 (A2), D6.1 (K), J1.1, Q3.3 (S), R15.2, RS1.1, TP1.1
/BAT_SH: D2.1 (A1), F5.1, Q1.4 (D), RS1.4
/BMS_3V3: C78.1, PS2.4 (+Vo), R168.1, R171.2, U25.8 (VDD2)
/BMS_R: J2.1, R169.1
/BMS_RI: R169.2, R171.1, U25.7 (VIA)
/BMS_RX: U15.6 (IO35), U25.2 (VOA)
/BMS_T: J2.2, R170.2
/BMS_TO: R170.1, U25.6 (VOB)
/BMS_TX: U15.30 (IO17), U25.3 (VIB)
/BRK_RES: C98.1, C99.1, D18.1 (K), R100.1, R110.1, U13.3 (IN), U13.4 (IN), U14.3 (IN), U14.4 (IN)
/BR_F_B1: F1.2, RS2.1
/BR_F_B2: F2.2, RS3.1
/BR_F_B3: F3.2, RS4.1
/BR_F_B4: F4.2, RS5.1
/BR_OUT_B1: J3.1, RS2.4
/BR_OUT_B2: J4.1, RS3.4
/BR_OUT_B3: J5.1, RS4.4
/BR_OUT_B4: J6.1, RS5.4
/BUSV_ADC: C73.1, R60.2, R154.1, U21.6 (AIN2)
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
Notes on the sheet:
1. ENTRÉE BATTERIE ET CONTACTEUR STATIQUE — TPS48100-Q1, 2 x IPB017N10N5LF tête-bêche
2. PRÉCHARGE — FET P piloté par l'ESP32, résistance 10 Ω / 25 W hors carte (J13)
3. HACHEUR DE FREINAGE — comparateur analogique alimenté par le bus, ON 42,5 V / OFF 41,8 V
4. BRANCHES MOTEUR — fusible MINI 58 V 25 A, shunt 2 mΩ + INA228 (0x41-0x44)
5. RAILS HÔTEL (amont contacteur, D2) — fusible, anti-inversion, 5 V 3,5 A, 12 V AUX 2 A, 12 V calculateur isolé, 3,3 V
6. SORTIES PROTÉGÉES — eFuses TPS2595x (C10), 5V_BRAKE dédié (D5) avec réservoir 2200 µF
7. ESP32 SAFETY, CAN, /SAFE (pull-up unique 1 kΩ + NF champignon, pull-down 10 kΩ), watchdog verrouillé (D7)
v2.0-draft — NE PAS FABRIQUER avant M1, M2, M10, M12, PACK_ID, P1-P3 et relecture par un électronicien
